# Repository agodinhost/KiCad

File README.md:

KiCad Projects
==============

GH-MXAlpas-mini
  Calavera GH-MXAlps-mini PCB

Matt3o-Teensy
  Designed to Matt3o StellBeauty custom keyboard, uses teensy 2.0.

Matt3o
  Designed to Matt3o StellBeauty custom keyboard, complete PCB.

ghkb-revb-alps
  ALPS version of Komar's GH60 rev b Keyboard.

ghpad-pos
  ghpad for one common chinese 5x5 keyboard pos sold at eBay (under delevelopment)

libraries
  common libraries, required by all projects above.

All these projects were written using KiCad 2013-05-31 BZR 4019.

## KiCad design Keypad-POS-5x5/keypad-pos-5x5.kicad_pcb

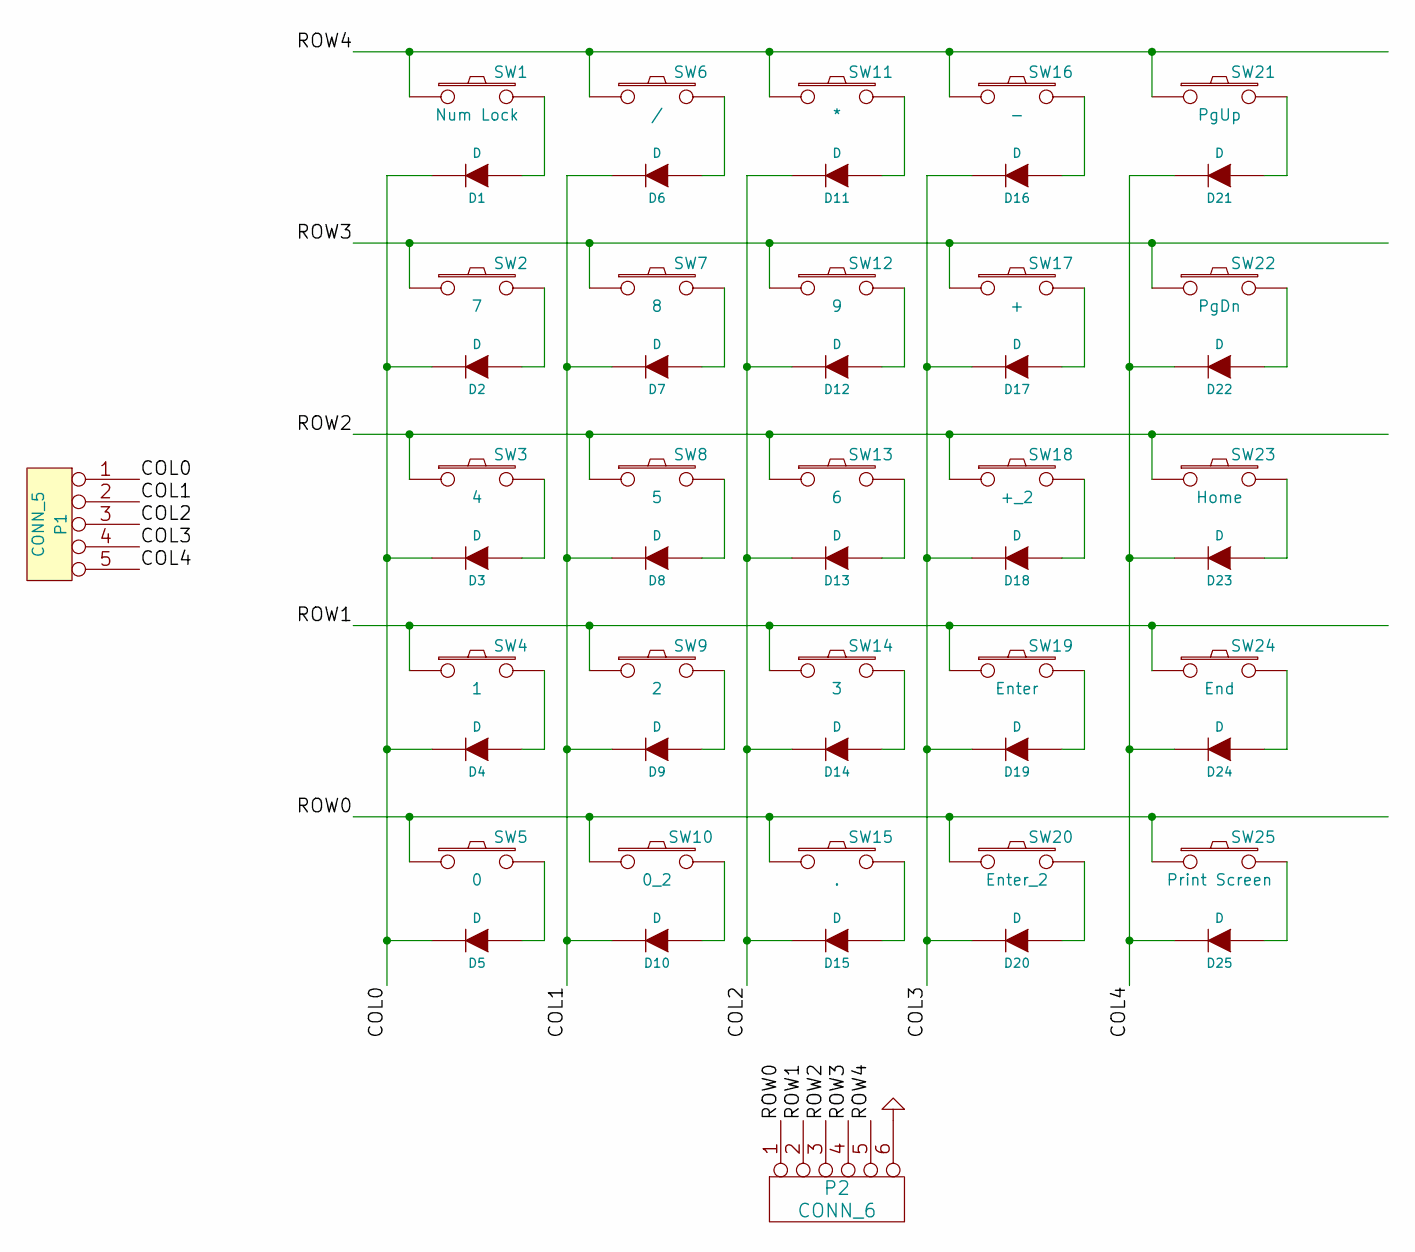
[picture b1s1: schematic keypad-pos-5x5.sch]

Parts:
D1, D2, D3, D4, D5, D6, D7, D8, D9, D10, D11, D12, D13, D14, D15, D16, D17, D18, D19, D20, D21, D22, D23, D24, D25: D
P1: CONN_5
P2: CONN_6
SW1: Num Lock
SW2: 7
SW3: 4
SW4: 1
SW5: 0
SW6: /
SW7: 8
SW8: 5
SW9: 2
SW10: 0_2
SW11: *
SW12: 9
SW13: 6
SW14: 3
SW15: .
SW16: -
SW17: +
SW18: +_2
SW19: Enter
SW20: Enter_2
SW21: PgUp
SW22: PgDn
SW23: Home
SW24: End
SW25: Print Screen

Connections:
/COL0: D1.2 (K), D2.2 (K), D3.2 (K), D4.2 (K), D5.2 (K), P1.1
/COL1: D6.2 (K), D7.2 (K), D8.2 (K), D9.2 (K), D10.2 (K), P1.2
/COL2: D11.2 (K), D12.2 (K), D13.2 (K), D14.2 (K), D15.2 (K), P1.3
/COL3: D16.2 (K), D17.2 (K), D18.2 (K), D19.2 (K), D20.2 (K), P1.4
/COL4: D21.2 (K), D22.2 (K), D23.2 (K), D24.2 (K), D25.2 (K), P1.5
/ROW0: P2.1, SW5.1, SW10.1, SW15.1, SW20.1, SW25.1
/ROW1: P2.2, SW4.1, SW9.1, SW14.1, SW19.1, SW24.1
/ROW2: P2.3, SW3.1, SW8.1, SW13.1, SW18.1, SW23.1
/ROW3: P2.4, SW2.1, SW7.1, SW12.1, SW17.1, SW22.1
/ROW4: P2.5, SW1.1, SW6.1, SW11.1, SW16.1, SW21.1
unnamed: D9.1 (A), SW9.2
unnamed: D20.1 (A), SW20.2
unnamed: D21.1 (A), SW21.2
unnamed: D22.1 (A), SW22.2
unnamed: D24.1 (A), SW24.2
unnamed: D25.1 (A), SW25.2
unnamed: D23.1 (A), SW23.2
unnamed: D16.1 (A), SW16.2
unnamed: D14.1 (A), SW14.2
unnamed: D12.1 (A), SW12.2
unnamed: D1.1 (A), SW1.2
unnamed: D6.1 (A), SW6.2
unnamed: D18.1 (A), SW18.2
unnamed: D17.1 (A), SW17.2
unnamed: D13.1 (A), SW13.2
unnamed: D5.1 (A), SW5.2
unnamed: D10.1 (A), SW10.2
unnamed: D15.1 (A), SW15.2
unnamed: D2.1 (A), SW2.2
unnamed: D19.1 (A), SW19.2
unnamed: D7.1 (A), SW7.2
unnamed: D8.1 (A), SW8.2
unnamed: D3.1 (A), SW3.2
unnamed: D4.1 (A), SW4.2
unnamed: D11.1 (A), SW11.2

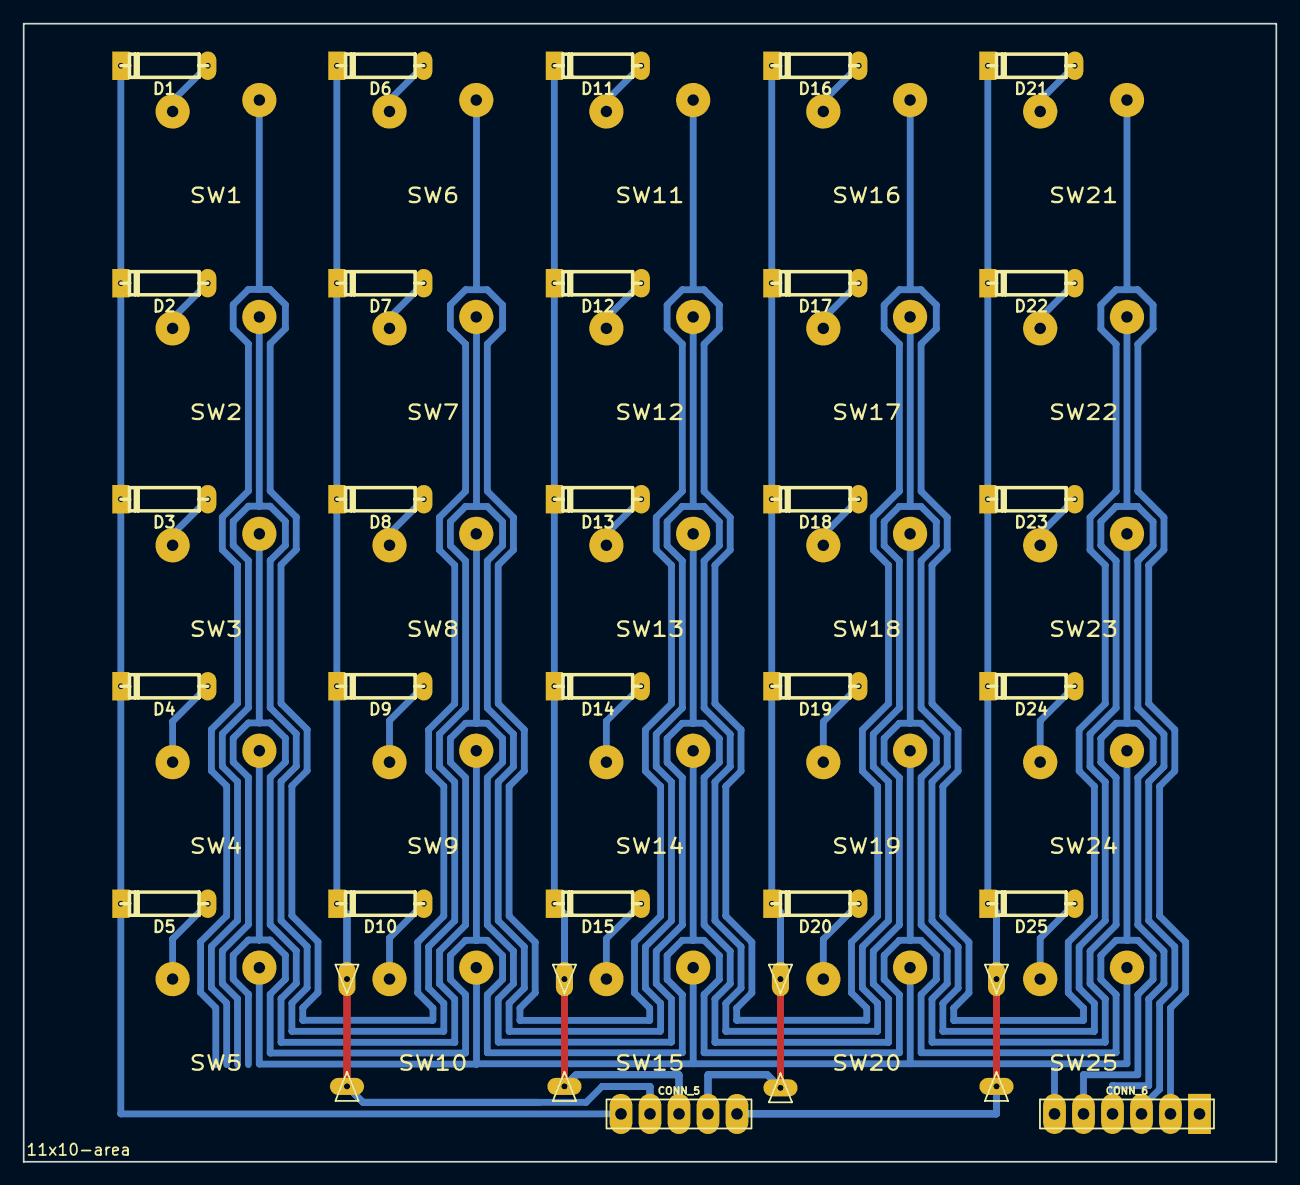
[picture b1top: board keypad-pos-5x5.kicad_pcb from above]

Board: 2 copper layers, 109.7 x 99.7 mm, 61 parts (0 on the bottom side), 35 nets.

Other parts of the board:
11x10-area: VAL**; 11x10-area
V1, V1#2, V1#5, V1#6: VIA-X; via-x
V1#3, V1#4, V1#7, V1#8: VIA-X2; via-x2

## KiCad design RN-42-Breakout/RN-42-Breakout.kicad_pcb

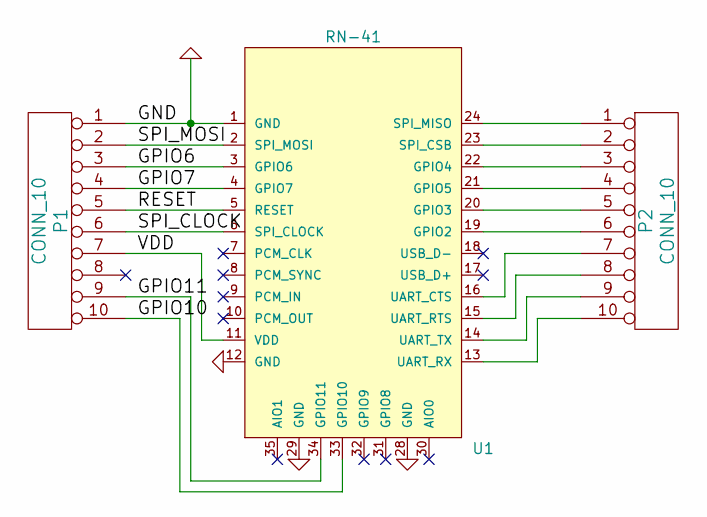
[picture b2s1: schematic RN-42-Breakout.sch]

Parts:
P1, P2: CONN_10
U1: RN-41

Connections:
/GPIO6: P1.3, U1.3 (GPIO6)
/GPIO7: P1.4, U1.4 (GPIO7)
/GPIO10: P1.10, U1.33 (GPIO10)
/GPIO11: P1.9, U1.34 (GPIO11)
/RESET: P1.5, U1.5 (RESET)
/SPI_CLOCK: P1.6, U1.6 (SPI_CLOCK)
/SPI_MOSI: P1.2, U1.2 (SPI_MOSI)
/VDD: P1.7, U1.11 (VDD)
GND: P1.1, U1.1 (GND), U1.12 (GND), U1.28 (GND), U1.29 (GND)
unnamed: P2.5, U1.20 (GPIO3)
unnamed: P2.10, U1.13 (UART_RX)
unnamed: P2.9, U1.14 (UART_TX)
unnamed: P2.8, U1.15 (UART_RTS)
unnamed: P2.7, U1.16 (UART_CTS)
unnamed: P2.6, U1.19 (GPIO2)
unnamed: P2.4, U1.21 (GPIO5)
unnamed: P2.3, U1.22 (GPIO4)
unnamed: P2.2, U1.23 (SPI_CSB)
unnamed: P2.1, U1.24 (SPI_MISO)

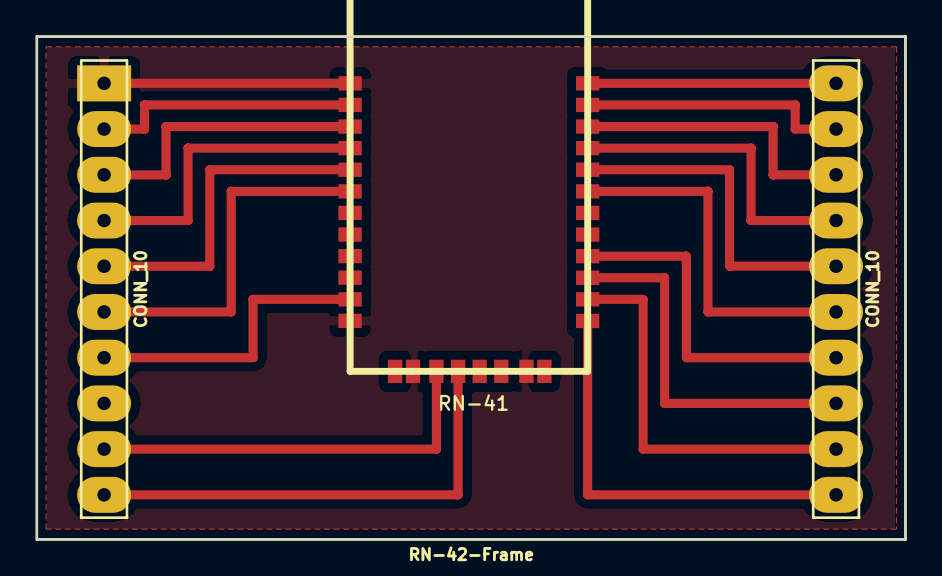
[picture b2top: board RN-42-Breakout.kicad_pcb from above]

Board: 2 copper layers, 48.2 x 27.9 mm, 4 parts (0 on the bottom side), 19 nets.

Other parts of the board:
Val**: RN-42-Frame

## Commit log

2013-03-25 first version
2013-03-25 ghkb-revb-alps added.
2013-03-25 first version.
2013-03-26 ghpad-pos
2013-03-26 libraries
2013-03-27 new version
2013-04-10 re-reouted the board. removed my extra library (the alps switches is now inside the mx1a module library).
2013-04-22 Matt3o board. first version.
2013-04-22 project update.
2013-04-22 cut layer. 286,5 x 96,5 mm.
2013-04-24 review moving diodes out of switch area.
2013-04-24 final version touches.
2013-04-26 Matt3o+Teensy 2.0.
2013-07-07 first version. testing the dimensions and hole positions.
2013-07-07 project descriptions.
2013-07-07 RN-42 breakout module. first version.
2013-07-07 sample project.
2013-07-07 bottom ground plane added.
2013-07-07 first version. single sided with jumpers.
2013-07-07 project deleted.
2013-07-07 kicadlibrary-master.zip added
2013-07-07 1U = 1.90mm
2013-07-07 ghkb-revb-alps renamed to GH60-Alps.
